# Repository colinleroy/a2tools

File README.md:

# Repository of stuff I write for my Apple //c

I'm having fun with this antiquity like it's 1989*!

The Apple //c was my first computer and I loved it dearly
for years, but to be honest, it served little purpose these
last years, only decorating the office. But then my wife woke
up a monster by suggesting we do the Advent of Code, and we
started, and then I thought

_"I should do it with the Apple //c!"_

One thing led to another and there are now quite a few things
here:
- a full featured Mastodon client ([homepage](https://www.colino.net/wordpress/en/mastodon-for-apple-ii/))
- a media player (mp3, video, webradios, ...) ([homepage](https://www.colino.net/wordpress/en/wozamp-an-apple-ii-music-and-video-player/))
- a Peertube and Youtube client ([homepage](https://www.colino.net/wordpress/en/woztubes-an-apple-ii-invidious-and-peertube-client/))
- a Shufflepuck clone, with two-players mode ([homepage](https://www.colino.net/wordpress/en/shufflepuck-cafe-for-apple-ii/))
- a Glider clone ([homepage](https://www.colino.net/wordpress/en/glider-for-apple-ii/))
- a Quicktake program, to get and view pictures from Quicktake cameras ([homepage](https://www.colino.net/wordpress/en/quicktake-for-apple-ii/))
- an FTP client
- a Telnet client
- an HomeAssistant frontend to control switches, heating, and view sensors' graphs.

## Building the Apple II programs

Install cc65:

```
git clone https://github.com/cc65/cc65.git
cd cc65
make
sudo make install
```

Build my things:

```
make
```

Create floppy images:

```
make dist
```

You can then transfer the images in dist/ using ADTPro, or putting them on a MicroSD card for your modern storage ([BurgerDisk](https://www.colino.net/wordpress/shop/apple-ii-hardware/burgerdisk/), [DominoDisk](https://www.colino.net/wordpress/shop/apple-ii-hardware/dominodisk/), [FloppyEmu](https://www.bigmessowires.com/floppy-emu/), etc).

## Building only the proxy

To build only the proxy, you can skip installing cc65. Install the build dependancies, then compile the proxy:

See [surl-server's README](./src/surl-server)

## Notes

The Apple 2 serial port is port 2 by default.

# Raspberry installation
For convenience, a pre-built surl-server is configured in the Raspberry image file,  surl-server-bullseye-YYYY-MM-DD-lite.img.gz , available in the releases.

Copy it to a microSD card:
```
gunzip surl-server-bullseye-YYYY-MM-DD-lite.img.gz
dd if=surl-server-bullseye-YYYY-MM-DD-lite.img of=/dev/mmcblk0 bs=4M status=progress
sync
```

Install the SD card into a Raspberry, connect Ethernet, connect USB/serial adapter and boot. Everything should be up and running if you have a DHCP server. 

You can ssh into the pi with the default Raspbian login, pi/raspberry. The Pi should get on the network as `surl-server.local`.

If you already have a running Raspberry that you'd want to use for this, you can instead add the following source and packages:

```
echo "deb https://apt-rpi.colino.net/debian bullseye main" | tee -a /etc/apt/sources.list.d/apt-rpi-colino-net.list
curl https://apt-rpi.colino.net/gpg.key | apt-key add -
apt update
apt install surl-server
```

*Yes, I know it's older than that. But I got mine in 1989, when I was nine.

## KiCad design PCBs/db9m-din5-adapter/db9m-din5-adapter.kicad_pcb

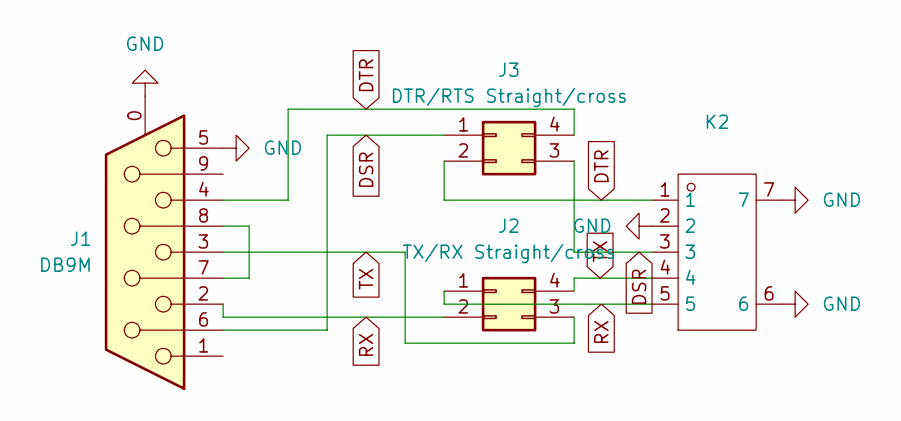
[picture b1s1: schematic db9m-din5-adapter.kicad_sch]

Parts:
J1: DB9M; DSUB-9_Pins_Horizontal_P2.77x2.84mm_EdgePinOffset7.70mm_Hou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
J2: TX/RX Straight/cross; PinHeader_2x02_P2.54mm_Vertical
J3: DTR/RTS Straight/cross; PinHeader_2x02_P2.54mm_Vertical
K2: CONN-TH_DIN-504-M10; Manufacturer Part DIN-504; LCSC Part Name DIN插座

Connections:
DSR: J1.6, J3.1, J3.3, K2.3
DTR: J1.4, J3.2, J3.4, K2.1
GND: J1.0 (PAD), J1.5, K2.2, K2.6, K2.7
unnamed: J1.7, J1.8
RX: J1.2, J2.1, J2.2, K2.5
TX: J1.3, J2.3, J2.4, K2.4

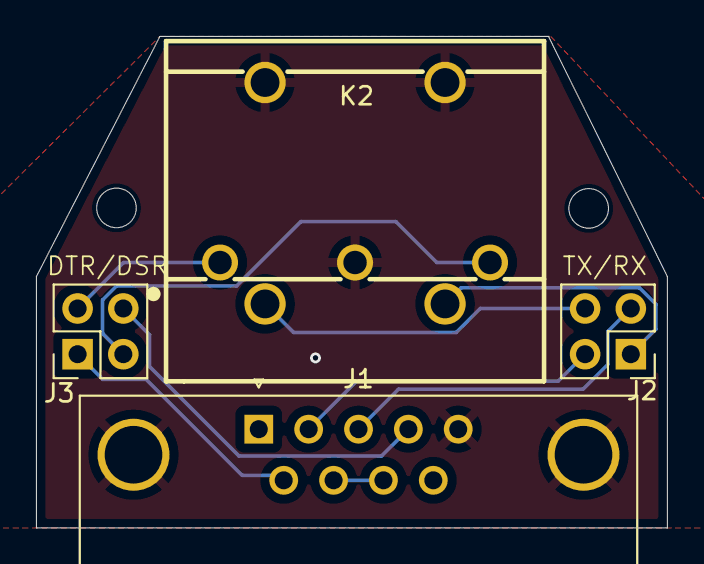
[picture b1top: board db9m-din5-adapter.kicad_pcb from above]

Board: 2 copper layers, 35.1 x 27.3 mm, 4 parts (0 on the bottom side), 6 nets.

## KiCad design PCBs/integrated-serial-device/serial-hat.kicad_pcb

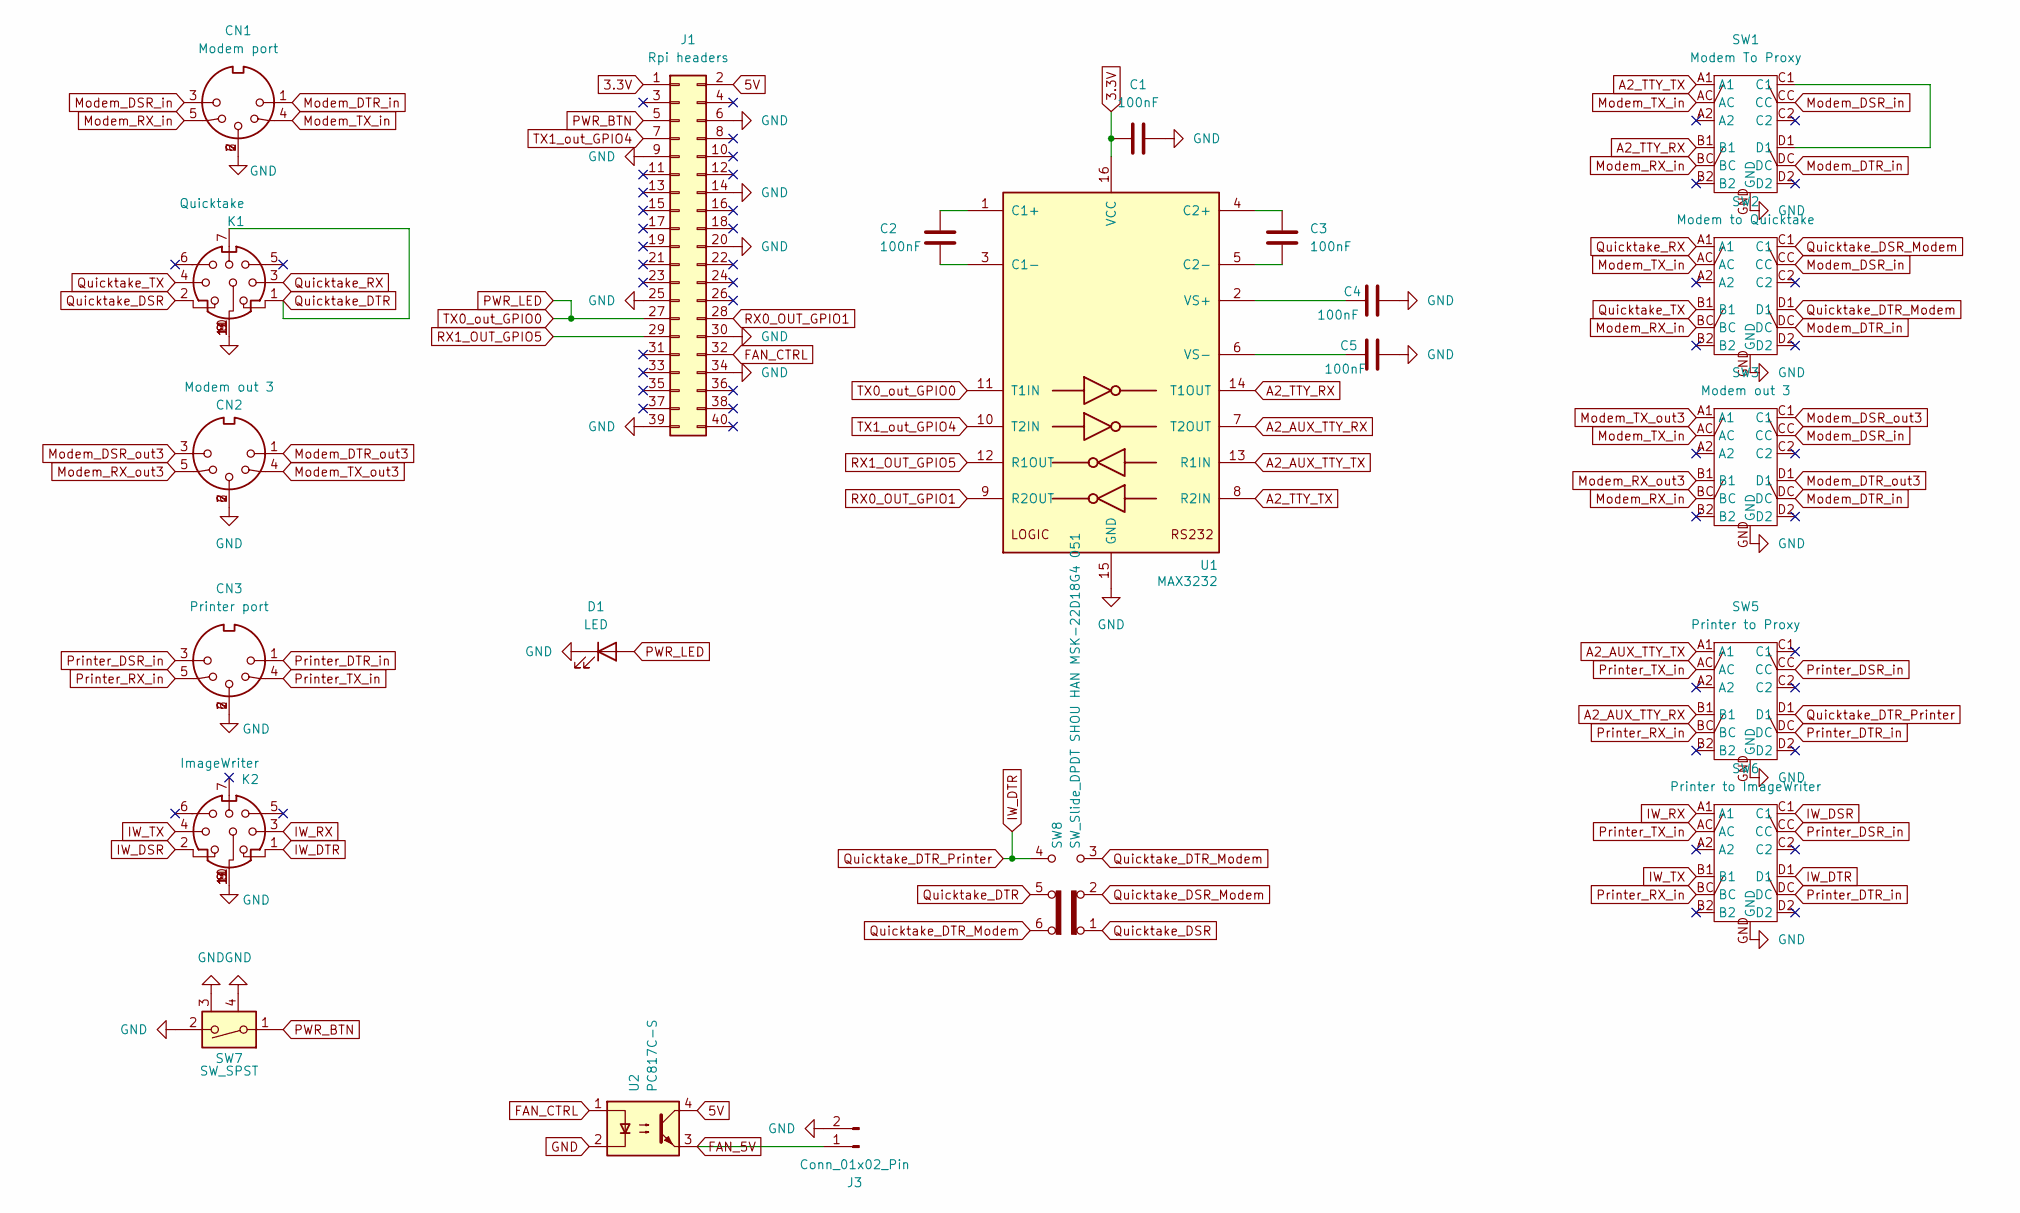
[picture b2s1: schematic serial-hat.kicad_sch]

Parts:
C1, C2, C3, C4, C5: 100nF; C_0603_1608Metric; LCSC C14663
CN1: Modem port; DIN-5-M C23689428; Manufacturer Part DIN-504; LCSC C23689428
CN2: Modem out 3; DIN-5-M C23689428; Manufacturer Part DIN-504; LCSC C23689428
CN3: Printer port; DIN-5-M C23689428; Manufacturer Part DIN-504; LCSC C23689428
D1: LED; LED_0603_1608Metric; LCSC C965807
J1: Rpi headers; PinSocket_2x20_P2.54mm_Vertical; LCSC C5124634
J3: Conn_01x02_Pin; PinHeader_1x02_P2.54mm_Vertical
K1: Quicktake; MINI-DIN8-F C20611694; Manufacturer Part DIN-802; LCSC Part Name DIN插座
K2: ImageWriter; MINI-DIN8-F C20611694; Manufacturer Part DIN-802; LCSC Part Name DIN插座
SW1: Modem To Proxy; 4PDT 12 pins Piano Switch
SW2: Modem to Quicktake; 4PDT 12 pins Piano Switch
SW3: Modem out 3; 4PDT 12 pins Piano Switch
SW5: Printer to Proxy; 4PDT 12 pins Piano Switch
SW6: Printer to ImageWriter; 4PDT 12 pins Piano Switch
SW7: SW_SPST; SPST momentary switch C6575016; LCSC C6575016
SW8: SW_Slide_DPDT SHOU HAN MSK-22D18G4 051; DPDT slide switch C7507433; LCSC C7507433
U1: MAX3232; SOIC-16_3.9x9.9mm_P1.27mm; LCSC C193666
U2: PC817C-S; PC817C-S C3008369; LCSC C3008369

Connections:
3.3V: C1.1, J1.1, U1.16 (VCC)
5V: J1.2, U2.4
A2_AUX_TTY_RX: SW5.B1, U1.7 (T2OUT)
A2_AUX_TTY_TX: SW5.A1, U1.13 (R1IN)
A2_TTY_RX: SW1.B1, U1.14 (T1OUT)
A2_TTY_TX: SW1.A1, U1.8 (R2IN)
FAN_5V: J3.1, U2.3
FAN_CTRL: J1.32, U2.1
GND: C1.2, C4.2, C5.2, CN1.2, CN1.6, CN1.7, CN2.2, CN2.6, CN2.7, CN3.2, CN3.6, CN3.7, D1.1 (K), J1.6, J1.9, J1.14, J1.20, J1.25, J1.30, J1.34, J1.39, J3.2, K1.8, K1.9, K1.10, K1.11, K2.8, K2.9, K2.10, K2.11, SW1.GND, SW2.GND, SW3.GND, SW5.GND, SW6.GND, SW7.2, SW7.3, SW7.4 (3), U1.15 (GND), U2.2
IW_DSR: K2.2, SW6.C1
IW_DTR: K2.1, SW5.D1, SW6.D1, SW8.4 (A)
IW_RX: K2.3, SW6.A1
IW_TX: K2.4, SW6.B1
Modem_DSR_in: CN1.3, SW1.CC, SW2.CC, SW3.CC
Modem_DSR_out3: CN2.3, SW3.C1
Modem_DTR_in: CN1.1, SW1.DC, SW2.DC, SW3.DC
Modem_DTR_out3: CN2.1, SW3.D1
Modem_RX_in: CN1.5, SW1.BC, SW2.BC, SW3.BC
Modem_RX_out3: CN2.5, SW3.B1
Modem_TX_in: CN1.4, SW1.AC, SW2.AC, SW3.AC
Modem_TX_out3: CN2.4, SW3.A1
unnamed: SW1.C1, SW1.D1
unnamed: C2.1, U1.1 (C1+)
unnamed: C2.2, U1.3 (C1-)
unnamed: C3.1, U1.4 (C2+)
unnamed: C3.2, U1.5 (C2-)
unnamed: C4.1, U1.2 (VS+)
unnamed: C5.1, U1.6 (VS-)
PWR_BTN: J1.5, SW7.1
PWR_LED: D1.2 (A), J1.27, U1.11 (T1IN)
Printer_DSR_in: CN3.3, SW5.CC, SW6.CC
Printer_DTR_in: CN3.1, SW5.DC, SW6.DC
Printer_RX_in: CN3.5, SW5.BC, SW6.BC
Printer_TX_in: CN3.4, SW5.AC, SW6.AC
Quicktake_DSR: K1.2, SW8.1 (A)
Quicktake_DSR_Modem: SW2.C1, SW8.2 (B)
Quicktake_DTR: K1.1, K1.7, SW8.5 (B)
Quicktake_DTR_Modem: SW2.D1, SW8.3 (C), SW8.6 (C)
Quicktake_RX: K1.3, SW2.A1
Quicktake_TX: K1.4, SW2.B1
RX0_OUT_GPIO1: J1.28, U1.9 (R2OUT)
RX1_OUT_GPIO5: J1.29, U1.12 (R1OUT)
TX1_out_GPIO4: J1.7, U1.10 (T2IN)

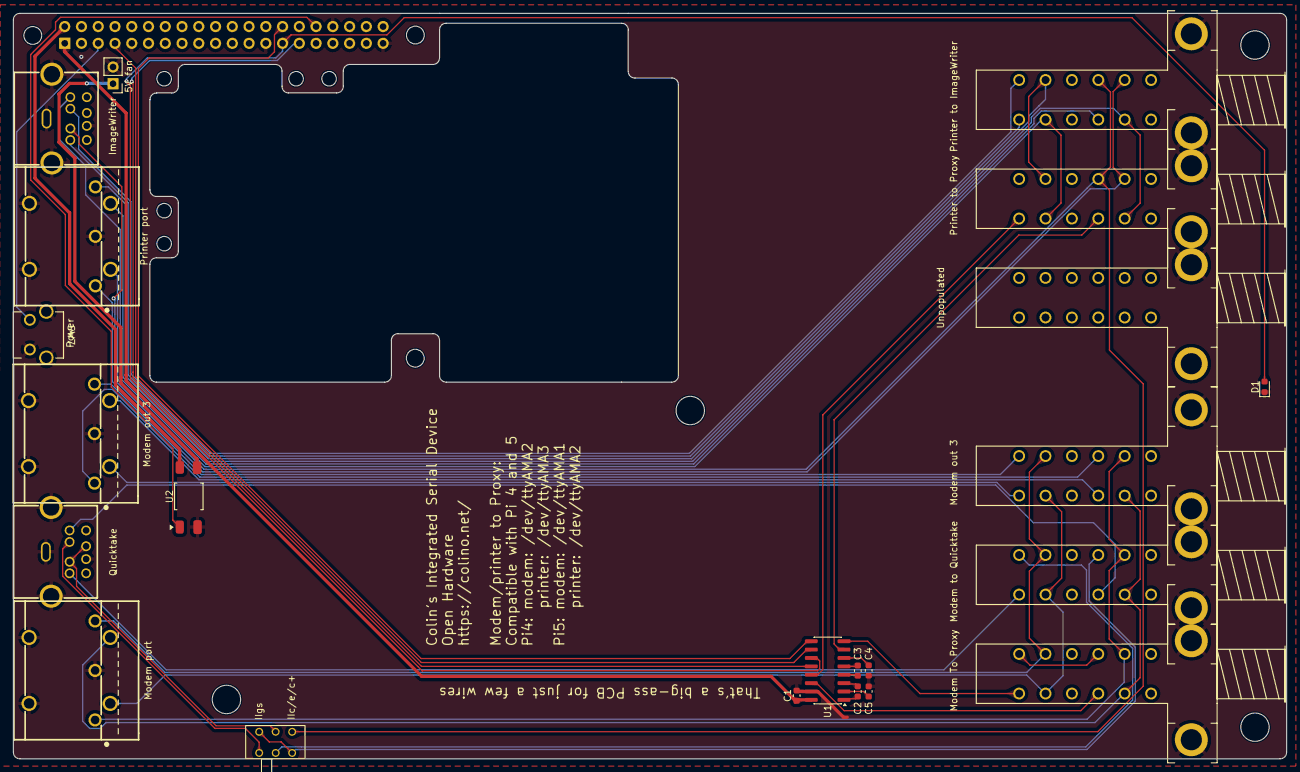
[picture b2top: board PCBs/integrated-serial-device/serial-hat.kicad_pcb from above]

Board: 2 copper layers, 193.0 x 113.0 mm, 30 parts (1 on the bottom side), 43 nets.

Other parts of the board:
MH1, MH3, MH4: MountingHole_2.7mm
MH2, MH5, MH7, MH8: MountingHole_4.3mm_M4
Unpopulated: 4PDT 12 pins Piano Switch

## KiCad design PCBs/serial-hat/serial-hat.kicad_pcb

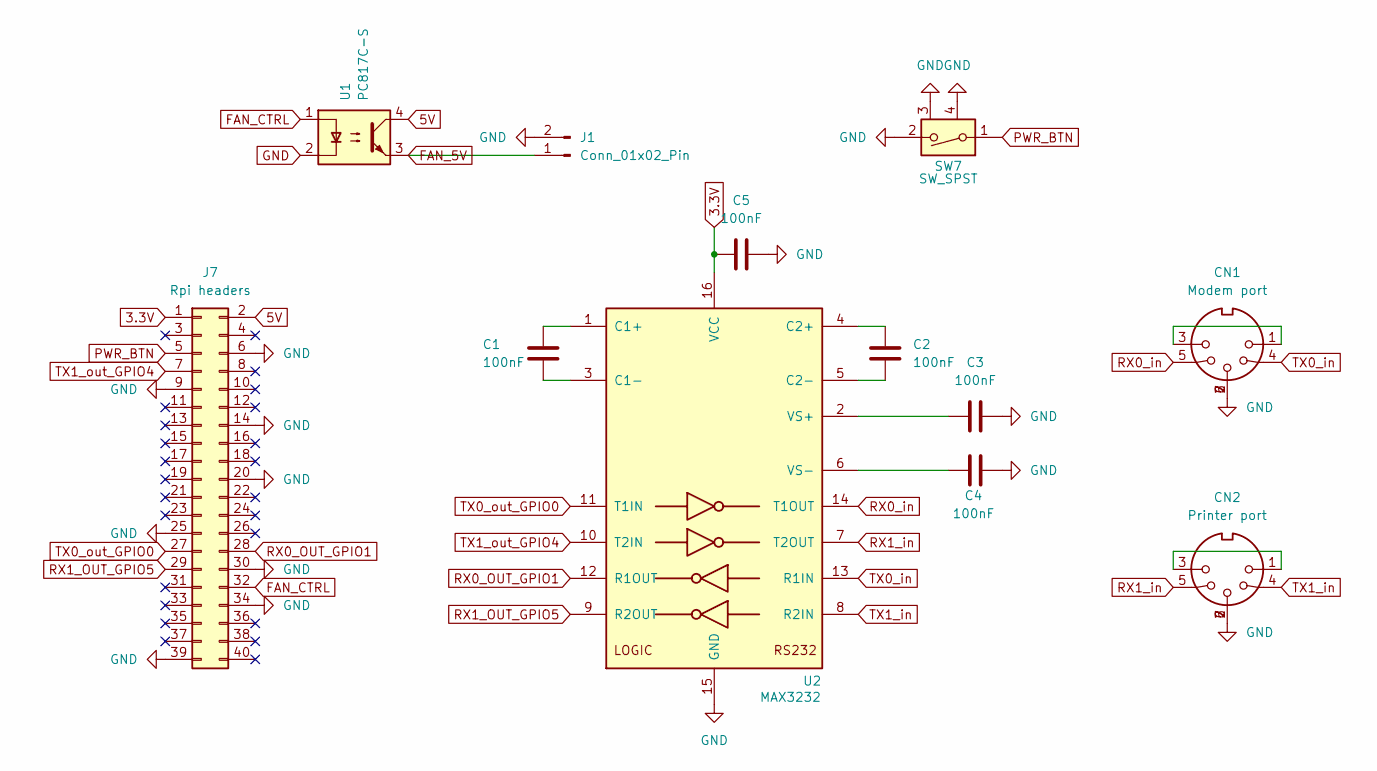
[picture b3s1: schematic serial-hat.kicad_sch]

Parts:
C1, C2, C3, C4, C5: 100nF; C_0603_1608Metric; LCSC C14663
CN1: Modem port; DIN-5-M C2939346; Manufacturer Part DIN-504; LCSC C2939346
CN2: Printer port; DIN-5-M C2939346; Manufacturer Part DIN-504; LCSC C2939346
J1: Conn_01x02_Pin; PinHeader_1x02_P2.54mm_Vertical
J7: Rpi headers; PinSocket_2x20_P2.54mm_Vertical; LCSC C5124634
SW7: SW_SPST; SPST momentary switch C6575016; LCSC C6575016
U1: PC817C-S; PC817C-S C3008369; LCSC C3008369
U2: MAX3232; SOIC-16_3.9x9.9mm_P1.27mm; LCSC C193666

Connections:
3.3V: C5.1, J7.1, U2.16 (VCC)
5V: J7.2, U1.4
FAN_5V: J1.1, U1.3
FAN_CTRL: J7.32, U1.1
GND: C3.2, C4.2, C5.2, CN1.2, CN1.6, CN1.7, CN2.2, CN2.6, CN2.7, J1.2, J7.6, J7.9, J7.14, J7.20, J7.25, J7.30, J7.34, J7.39, SW7.2, SW7.3, SW7.4 (3), U1.2, U2.15 (GND)
unnamed: CN1.1, CN1.3
unnamed: CN2.1, CN2.3
unnamed: C1.1, U2.1 (C1+)
unnamed: C1.2, U2.3 (C1-)
unnamed: C2.1, U2.4 (C2+)
unnamed: C2.2, U2.5 (C2-)
unnamed: C3.1, U2.2 (VS+)
unnamed: C4.1, U2.6 (VS-)
PWR_BTN: J7.5, SW7.1
RX0_OUT_GPIO1: J7.28, U2.12 (R1OUT)
RX0_in: CN1.5, U2.14 (T1OUT)
RX1_OUT_GPIO5: J7.29, U2.9 (R2OUT)
RX1_in: CN2.5, U2.7 (T2OUT)
TX0_in: CN1.4, U2.13 (R1IN)
TX0_out_GPIO0: J7.27, U2.11 (T1IN)
TX1_in: CN2.4, U2.8 (R2IN)
TX1_out_GPIO4: J7.7, U2.10 (T2IN)

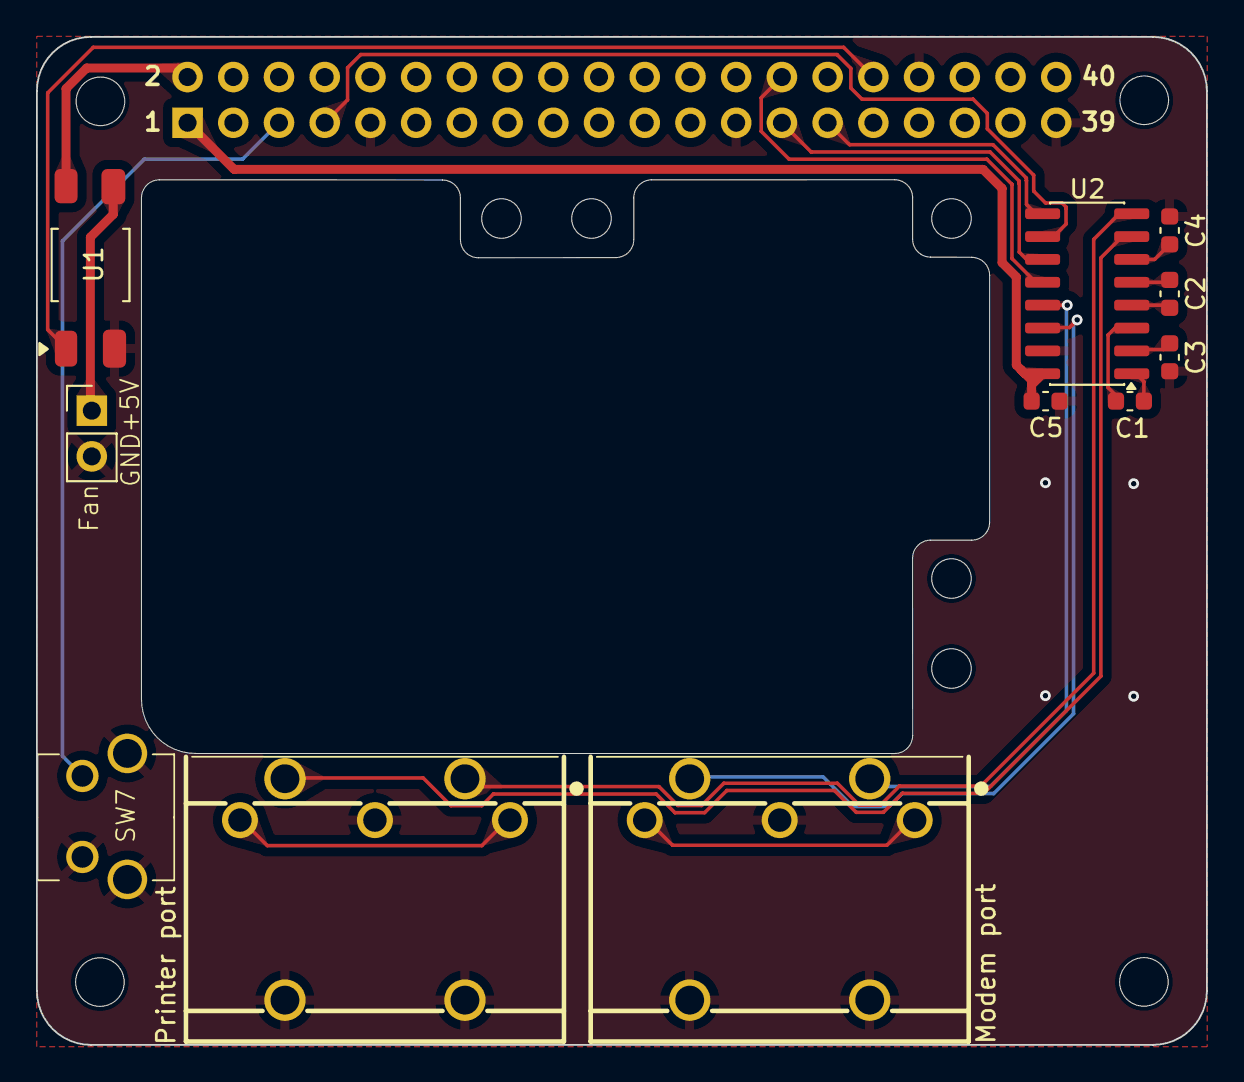
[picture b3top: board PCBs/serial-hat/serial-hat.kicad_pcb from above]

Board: 2 copper layers, 65.0 x 56.0 mm, 12 parts (1 on the bottom side), 22 nets.

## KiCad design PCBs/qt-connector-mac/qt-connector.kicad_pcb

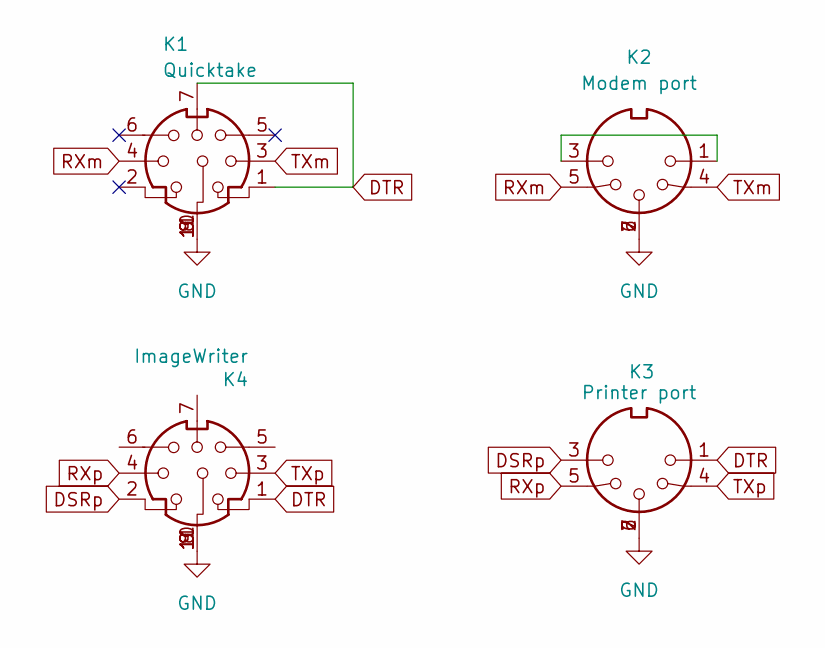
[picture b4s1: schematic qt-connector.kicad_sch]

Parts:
K1: Quicktake; MINI-DIN8-F C20611694; Manufacturer Part DIN-802; LCSC Part Name DIN插座
K2: Modem port; DIN-5-M C23689428; Manufacturer Part DIN-504; LCSC Part Name DIN插座
K3: Printer port; DIN-5-M C23689428; Manufacturer Part DIN-504; LCSC Part Name DIN插座
K4: ImageWriter; MINI-DIN8-F C20611694; Manufacturer Part DIN-802; LCSC Part Name DIN插座

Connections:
DSRp: K3.3, K4.2
DTR: K1.1, K1.7, K3.1, K4.1
GND: K1.8, K1.9, K1.10, K1.11, K2.2, K2.6, K2.7, K3.2, K3.6, K3.7, K4.8, K4.9, K4.10, K4.11
unnamed: K2.1, K2.3
RXm: K1.4, K2.5
RXp: K3.5, K4.4
TXm: K1.3, K2.4
TXp: K3.4, K4.3

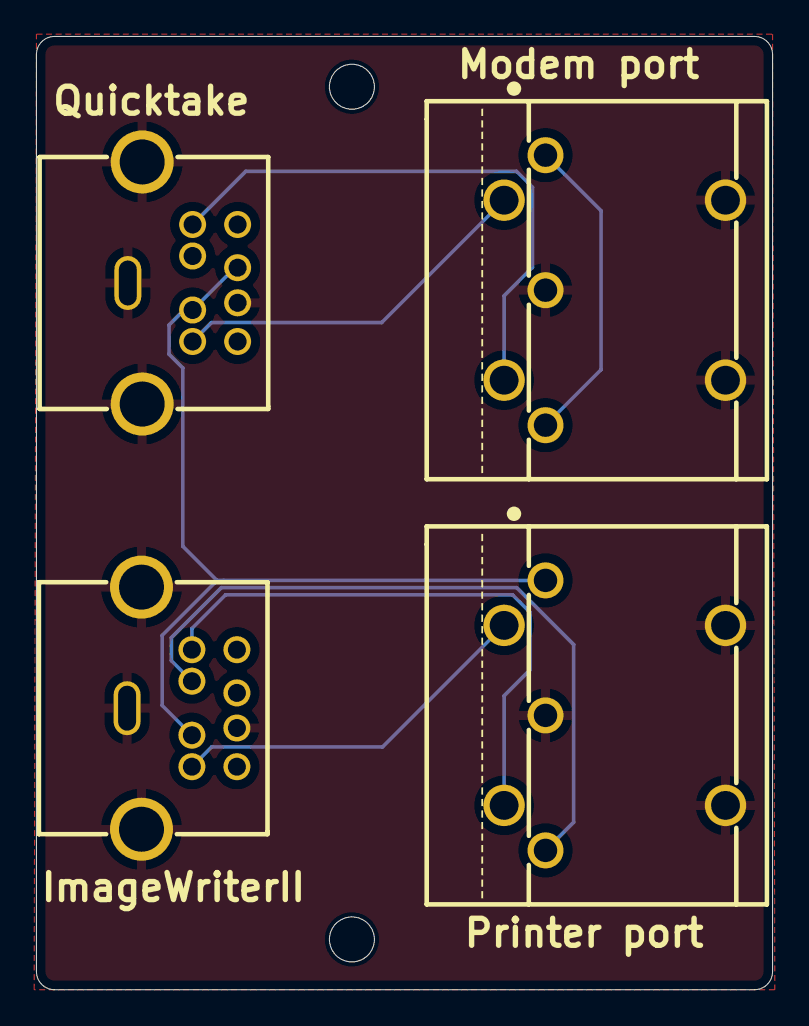
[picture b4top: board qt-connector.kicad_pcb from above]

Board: 2 copper layers, 40.9 x 53.0 mm, 4 parts (0 on the bottom side), 8 nets.

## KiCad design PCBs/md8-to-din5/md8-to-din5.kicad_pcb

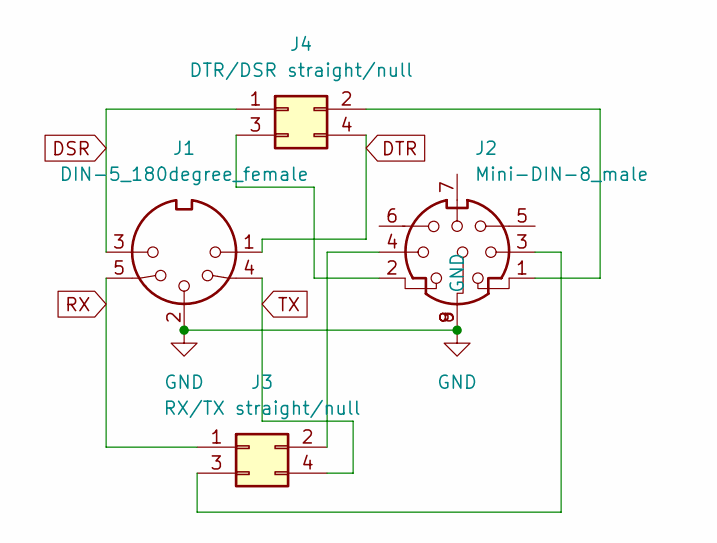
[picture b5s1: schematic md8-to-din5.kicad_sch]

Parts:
J1: DIN-5_180degree_female; DIN-5-F
J2: Mini-DIN-8_male; Mini-DIN8
J3: RX/TX straight/null; PinHeader_2x02_P2.54mm_Vertical
J4: DTR/DSR straight/null; PinHeader_2x02_P2.54mm_Vertical

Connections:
GND: J1.2, J2.8, J2.9 (GND)
unnamed: J1.5, J3.1
unnamed: J2.4, J3.2
unnamed: J2.3, J3.3
unnamed: J1.4, J3.4
unnamed: J1.3, J4.1
unnamed: J2.1, J4.2
unnamed: J2.2, J4.3
unnamed: J1.1, J4.4

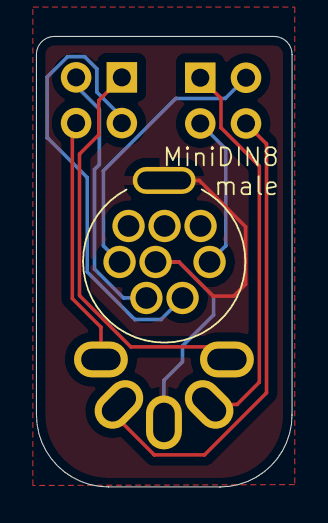
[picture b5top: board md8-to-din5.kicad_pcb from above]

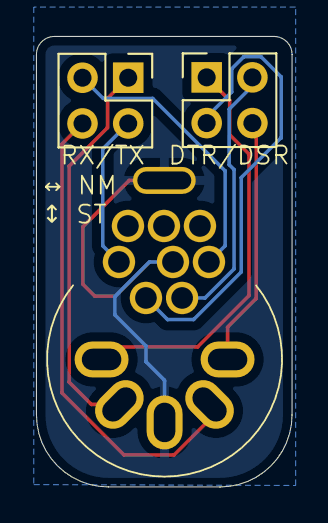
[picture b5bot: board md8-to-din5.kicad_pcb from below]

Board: 2 copper layers, 14.2 x 25.0 mm, 4 parts (3 on the bottom side), 9 nets.

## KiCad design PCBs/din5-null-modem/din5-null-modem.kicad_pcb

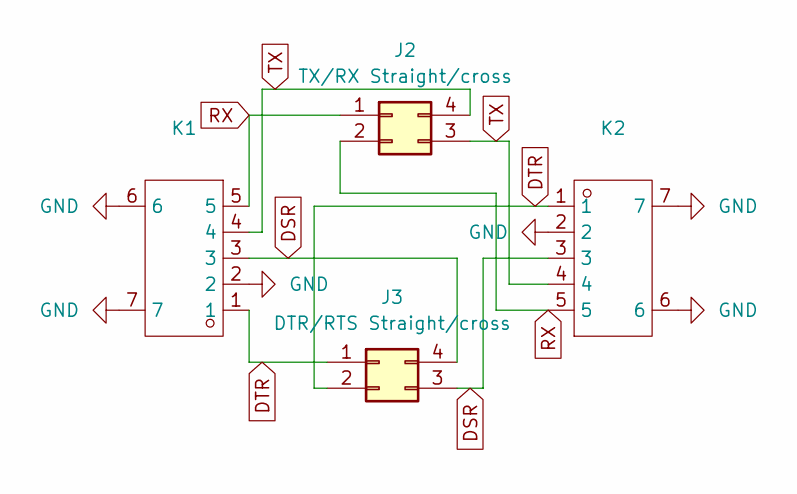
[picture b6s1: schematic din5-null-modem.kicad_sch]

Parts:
J2: TX/RX Straight/cross; PinHeader_2x02_P2.54mm_Vertical
J3: DTR/RTS Straight/cross; PinHeader_2x02_P2.54mm_Vertical
K1, K2: CONN-TH_DIN-504-M10; Manufacturer Part DIN-504; LCSC Part Name DIN插座

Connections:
DSR: J3.3, J3.4, K1.3, K2.3
DTR: J3.1, J3.2, K1.1, K2.1
GND: K1.2, K1.6, K1.7, K2.2, K2.6, K2.7
RX: J2.1, J2.2, K1.5, K2.5
TX: J2.3, J2.4, K1.4, K2.4

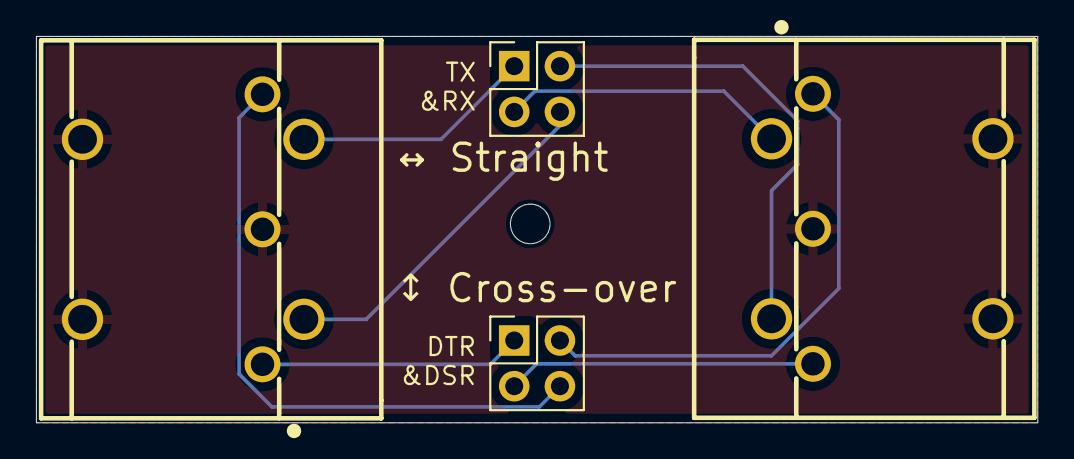
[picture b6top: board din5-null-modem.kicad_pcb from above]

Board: 2 copper layers, 55.6 x 21.5 mm, 4 parts (0 on the bottom side), 5 nets.

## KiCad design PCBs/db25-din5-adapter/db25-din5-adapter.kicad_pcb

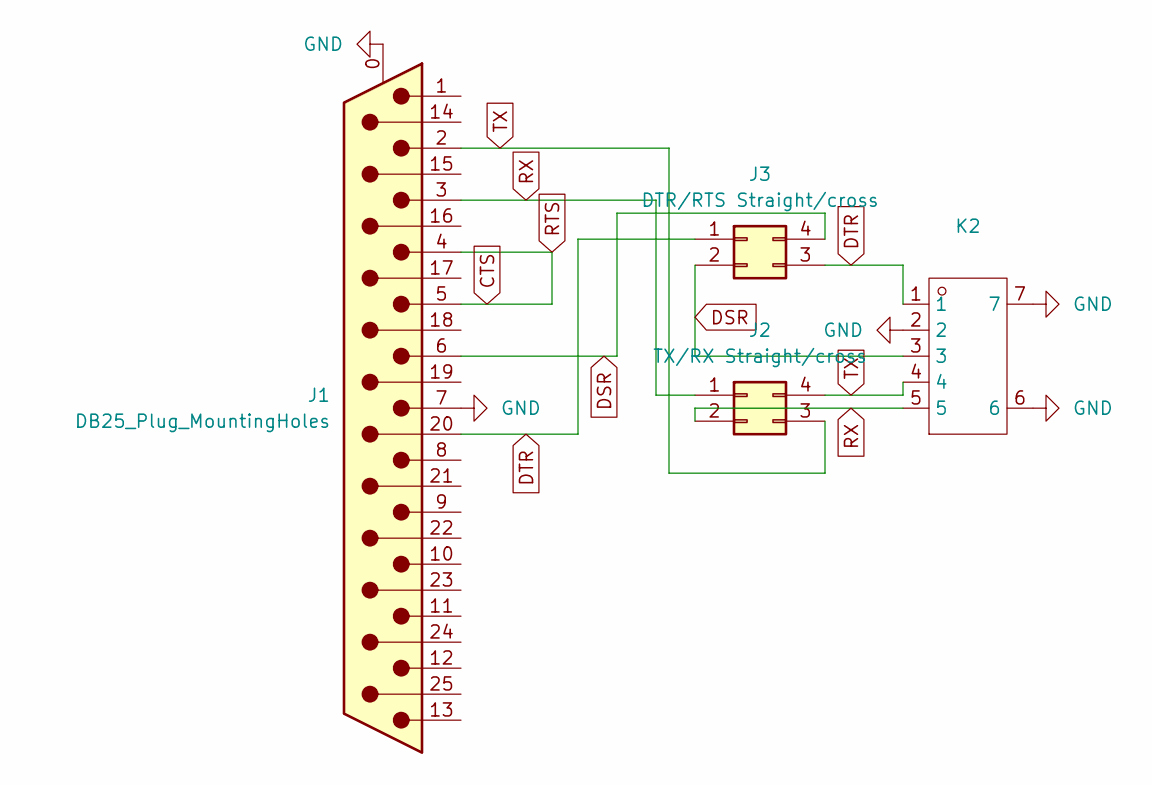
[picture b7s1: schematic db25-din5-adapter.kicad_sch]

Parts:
J1: DB25_Plug_MountingHoles; DSUB-25_Male_Horizontal_P2.77x2.84mm_EdgePinOffset4.94mm_Ho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
J2: TX/RX Straight/cross; PinHeader_2x02_P2.54mm_Vertical
J3: DTR/RTS Straight/cross; PinHeader_2x02_P2.54mm_Vertical
K2: CONN-TH_DIN-504-M10; Manufacturer Part DIN-504; LCSC Part Name DIN插座

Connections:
CTS: J1.4, J1.5
DSR: J1.6, J3.2, J3.4, K2.3
DTR: J1.20, J3.1, J3.3, K2.1
GND: J1.0 (PAD), J1.7, K2.2, K2.6, K2.7
RX: J1.3, J2.1, J2.2, K2.5
TX: J1.2, J2.3, J2.4, K2.4

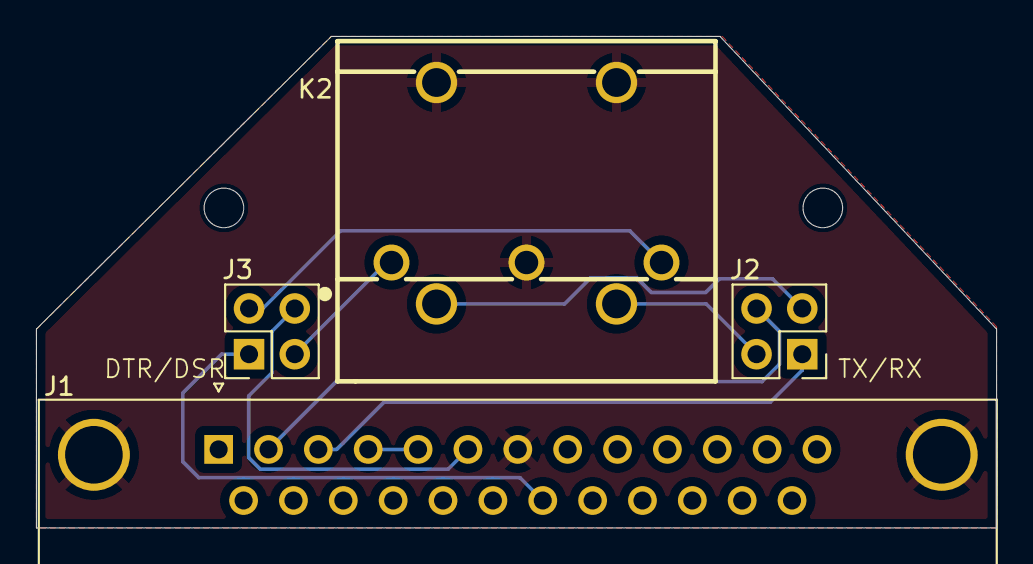
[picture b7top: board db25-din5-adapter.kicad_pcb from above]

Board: 2 copper layers, 53.3 x 27.3 mm, 4 parts (0 on the bottom side), 6 nets.

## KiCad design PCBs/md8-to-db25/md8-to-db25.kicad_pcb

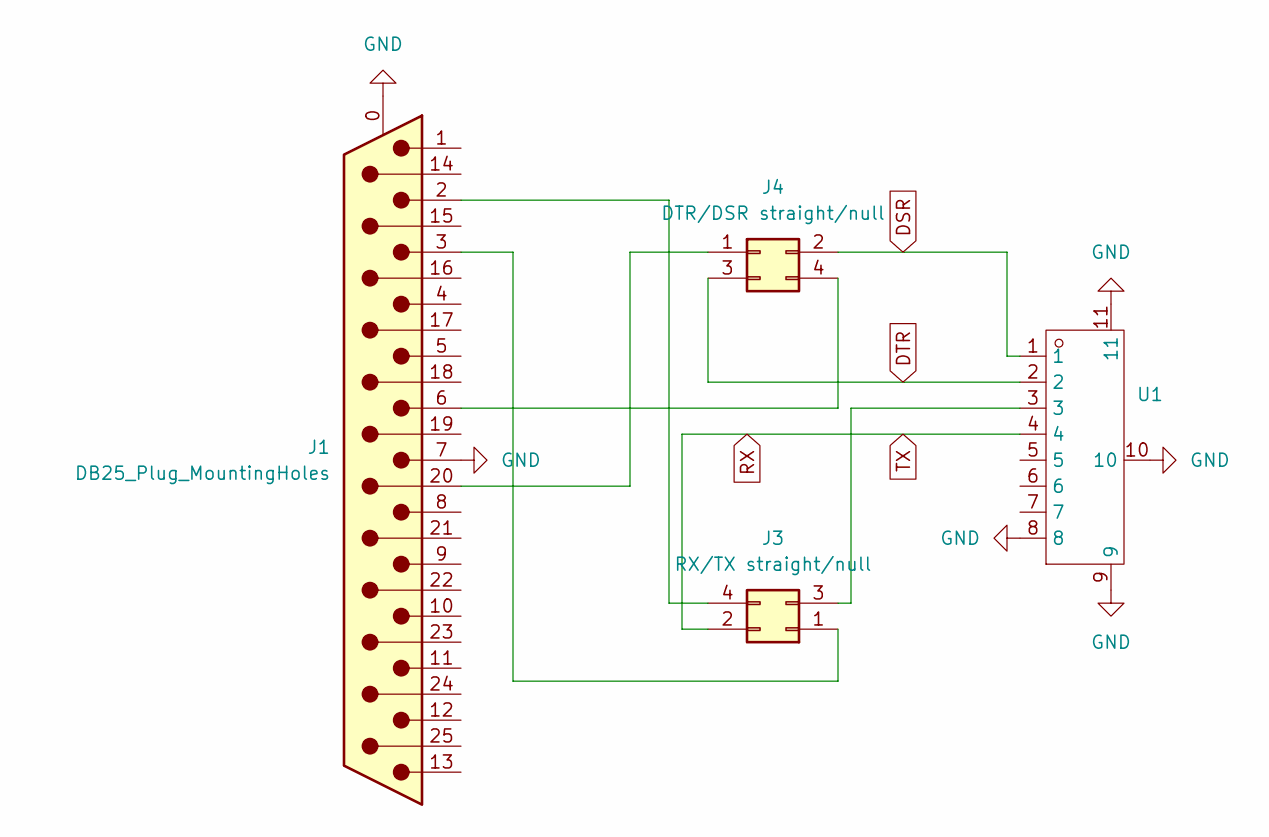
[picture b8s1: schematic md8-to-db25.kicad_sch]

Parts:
J1: DB25_Plug_MountingHoles; DSUB-25_Male_Horizontal_P2.77x2.84mm_EdgePinOffset4.94mm_Ho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
J3: RX/TX straight/null; PinHeader_2x02_P2.54mm_Vertical
J4: DTR/DSR straight/null; PinHeader_2x02_P2.54mm_Vertical
U1: MINI-DIN8; Manufacturer Part DIN-802; LCSC Part Name DIN插座

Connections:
DSR: J4.2, U1.1
DTR: J4.3, U1.2
GND: J1.0 (PAD), J1.7, U1.8, U1.9, U1.10, U1.11
unnamed: J1.20, J4.1
unnamed: J1.3, J3.1
unnamed: J3.3, U1.3
unnamed: J1.2, J3.4
unnamed: J1.6, J4.4
RX: J3.2, U1.4

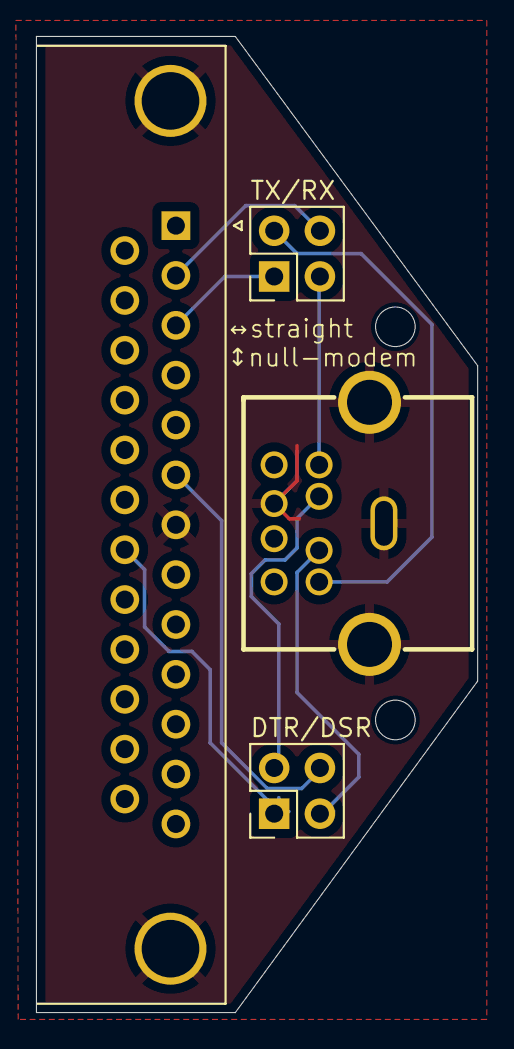
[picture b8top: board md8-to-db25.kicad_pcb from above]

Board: 2 copper layers, 24.5 x 54.2 mm, 4 parts (0 on the bottom side), 9 nets.
